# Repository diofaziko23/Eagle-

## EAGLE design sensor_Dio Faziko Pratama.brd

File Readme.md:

<!-- More info, tips and tricks for making GitHub Profile README can be found in my article at https://towardsdatascience.com/build-a-stunning-readme-for-your-github-profile-9b80434fe5d7 -->
<h1 align="center">Hi 👋, IM DIO FAZIKO PRATAMA</h1>
<h3 align="center">I am a student of the electronic engineering study program, Yogyakarta State University</h3>

- 🔭 I’m currently working on [Arduino and Artificial Intelligence](https://github.com/diofaziko23/arduino-project)
- 🔭 I’m currently working on [Arduino and Internet of Things](https://github.com/diofaziko23/arduino-project)
- 🌱 I’m currently learning **programming language,**
- 👨‍💻 All of my projects are available at [https://github.com/diofaziko23?tab=repositories](https://github.com/diofaziko23?tab=repositories)
- 📫 How to reach me **diofaziko.2021@student.uny.ac.id**.

<h3 align="left">Connect with me:</h3>
<p align="left">

</p>
<p align="left">

<h3 align="left">Languages and Tools:</h3>
<p align="left">              </p>

<p >&nbsp;</p>
<p align="left" >&nbsp;</p>

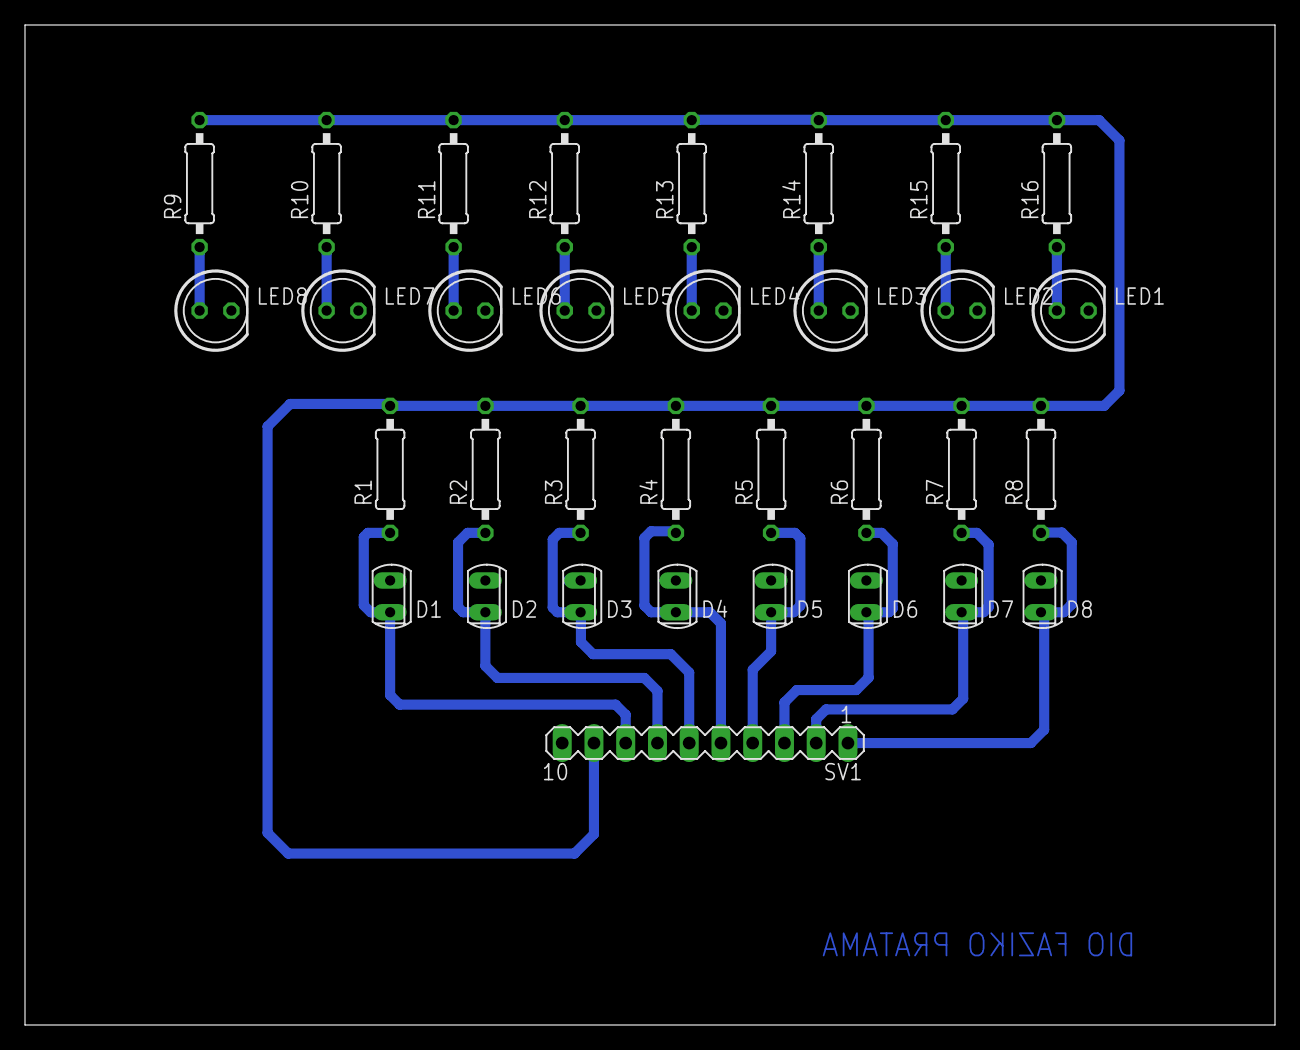
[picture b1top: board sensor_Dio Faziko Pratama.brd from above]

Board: 2 copper layers, 100.0 x 80.0 mm, 33 parts (0 on the bottom side), 18 nets.

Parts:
D1, D2, D3, D4, D5, D6, D7, D8: PhotoDioda; SFH225
LED1, LED2, LED3, LED4, LED5, LED6, LED7, LED8: LED putih SB; LED5MM
R1, R2, R3, R4, R5, R6, R7, R8: 0207/10
R9, R10, R11, R12, R13, R14, R15, R16: 330; 0207/10
SV1: MA10-1

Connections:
GND: D1.A, D2.A, D3.A, D4.A, D5.A, D6.A, D7.A, D8.A, LED1.K, LED2.K, LED3.K, LED4.K, LED5.K, LED6.K, LED7.K, LED8.K, SV1.10
unnamed: LED7.A, R10.1
unnamed: D7.K, R7.1, SV1.2
unnamed: D8.K, R8.1, SV1.1
unnamed: D1.K, R1.1, SV1.8
unnamed: D2.K, R2.1, SV1.7
unnamed: D3.K, R3.1, SV1.6
unnamed: D5.K, R5.1, SV1.4
unnamed: D4.K, R4.1, SV1.5
unnamed: D6.K, R6.1, SV1.3
unnamed: LED6.A, R11.1
unnamed: LED5.A, R12.1
unnamed: LED4.A, R13.1
unnamed: LED3.A, R14.1
unnamed: LED2.A, R15.1
unnamed: LED1.A, R16.1
unnamed: LED8.A, R9.1
VCC: R1.2, R2.2, R3.2, R4.2, R5.2, R6.2, R7.2, R8.2, R9.2, R10.2, R11.2, R12.2, R13.2, R14.2, R15.2, R16.2, SV1.9

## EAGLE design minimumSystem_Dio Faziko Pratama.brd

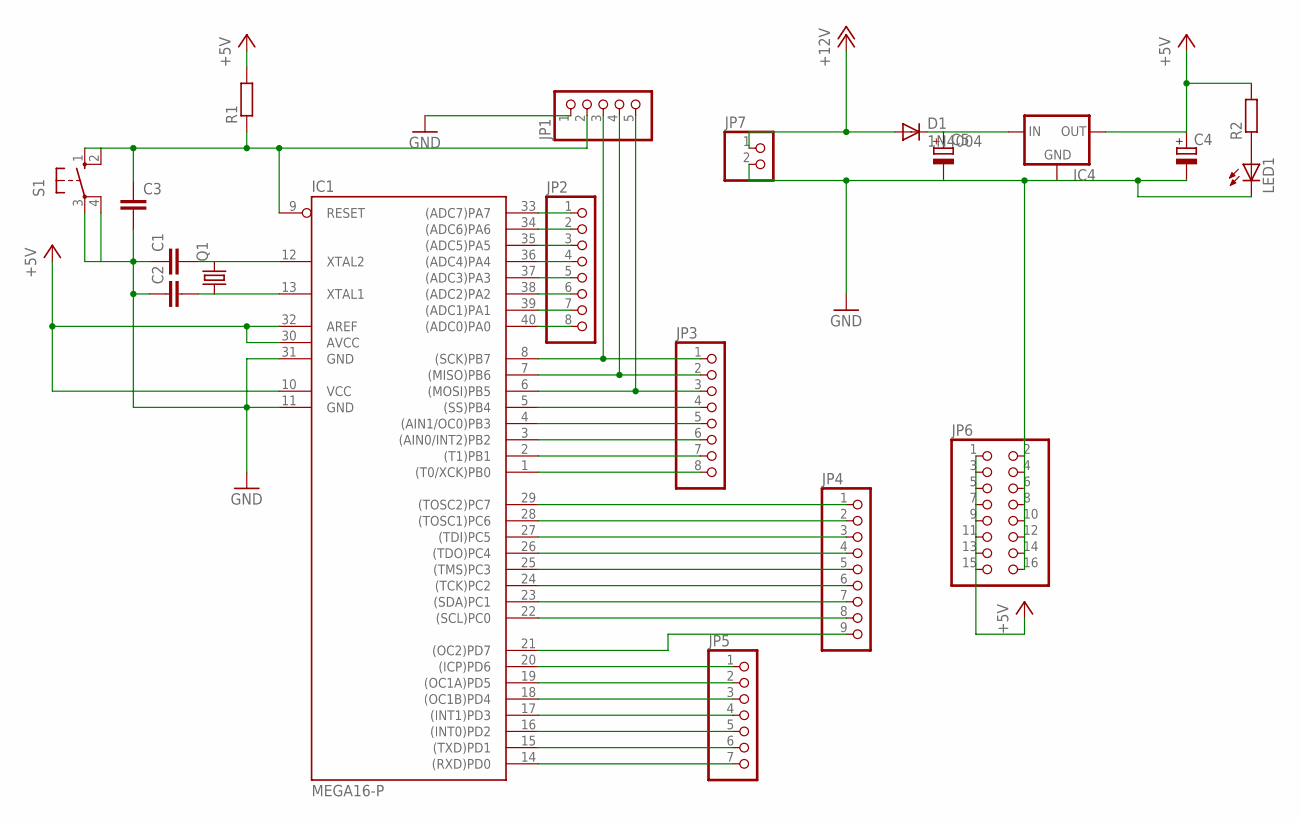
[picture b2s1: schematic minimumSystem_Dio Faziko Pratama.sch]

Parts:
C1, C2: C-EU025-024X044; C025-024X044
C3: C-EU050-025X075; C050-025X075
C4, C5: CPOL-EUE2.5-5; E2,5-5
D1: 1N4004; DO41-10
IC1: MEGA16-P; DIL40
IC4: 78XXS
JP1: PINHD-1X5; 1X05
JP2, JP3: PINHD-1X8; 1X08
JP4: PINHD-1X9; 1X09
JP5: PINHD-1X7; 1X07
JP6: PINHD-2X8; 2X08
JP7: PINHD-1X2; 1X02
LED1: LED5MM
Q1: CRYSTALHC49U-V; HC49U-V
R1, R2: R-EU_0204/7; 0204/7
S1: 10-XX; B3F-10XX

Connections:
+5V: C4.+, IC1.10 (VCC), IC1.30 (AVCC), IC1.32 (AREF), IC4.OUT, JP6.1, JP6.3, JP6.5, JP6.7, JP6.9, JP6.11, JP6.13, JP6.15, R1.2, R2.2
+12V: D1.A, JP7.1
C0: IC1.22 ((SCL)PC0), JP4.8
C1: IC1.23 ((SDA)PC1), JP4.7
C2: IC1.24 ((TCK)PC2), JP4.6
C3: IC1.25 ((TMS)PC3), JP4.5
D7: IC1.14 ((RXD)PD0), JP5.7
GND: C1.1, C2.1, C3.2, C4.-, C5.-, IC1.11 (GND), IC1.31 (GND), IC4.GND, JP1.1, JP6.2, JP6.4, JP6.6, JP6.8, JP6.10, JP6.12, JP6.14, JP6.16, JP7.2, LED1.K (C), S1.3, S1.4 (P1)
unnamed: IC1.33 ((ADC7)PA7), JP2.1
unnamed: IC1.34 ((ADC6)PA6), JP2.2
unnamed: IC1.35 ((ADC5)PA5), JP2.3
unnamed: IC1.36 ((ADC4)PA4), JP2.4
unnamed: IC1.37 ((ADC3)PA3), JP2.5
unnamed: IC1.38 ((ADC2)PA2), JP2.6
unnamed: IC1.39 ((ADC1)PA1), JP2.7
unnamed: IC1.40 ((ADC0)PA0), JP2.8
unnamed: IC1.29 ((TOSC2)PC7), JP4.1
unnamed: IC1.28 ((TOSC1)PC6), JP4.2
unnamed: IC1.27 ((TDI)PC5), JP4.3
unnamed: IC1.5 ((SS)PB4), JP3.4
unnamed: IC1.20 ((ICP)PD6), JP5.1
unnamed: IC1.19 ((OC1A)PD5), JP5.2
unnamed: IC1.26 ((TDO)PC4), JP4.4
unnamed: IC1.6 ((MOSI)PB5), JP1.5, JP3.3
unnamed: IC1.4 ((AIN1/OC0)PB3), JP3.5
unnamed: IC1.3 ((AIN0/INT2)PB2), JP3.6
unnamed: IC1.2 ((T1)PB1), JP3.7
unnamed: IC1.1 ((T0/XCK)PB0), JP3.8
unnamed: C5.+, D1.C, IC4.IN
unnamed: IC1.15 ((TXD)PD1), JP5.6
unnamed: IC1.16 ((INT0)PD2), JP5.5
unnamed: IC1.17 ((INT1)PD3), JP5.4
unnamed: C3.1, IC1.9 (RESET), JP1.2, R1.1, S1.1 (S), S1.2 (S1)
unnamed: IC1.18 ((OC1B)PD4), JP5.3
unnamed: C1.2, IC1.12 (XTAL2), Q1.2
unnamed: C2.2, IC1.13 (XTAL1), Q1.1
unnamed: LED1.A, R2.1
unnamed: IC1.8 ((SCK)PB7), JP1.3, JP3.1
unnamed: IC1.7 ((MISO)PB6), JP1.4, JP3.2
RS: IC1.21 ((OC2)PD7), JP4.9

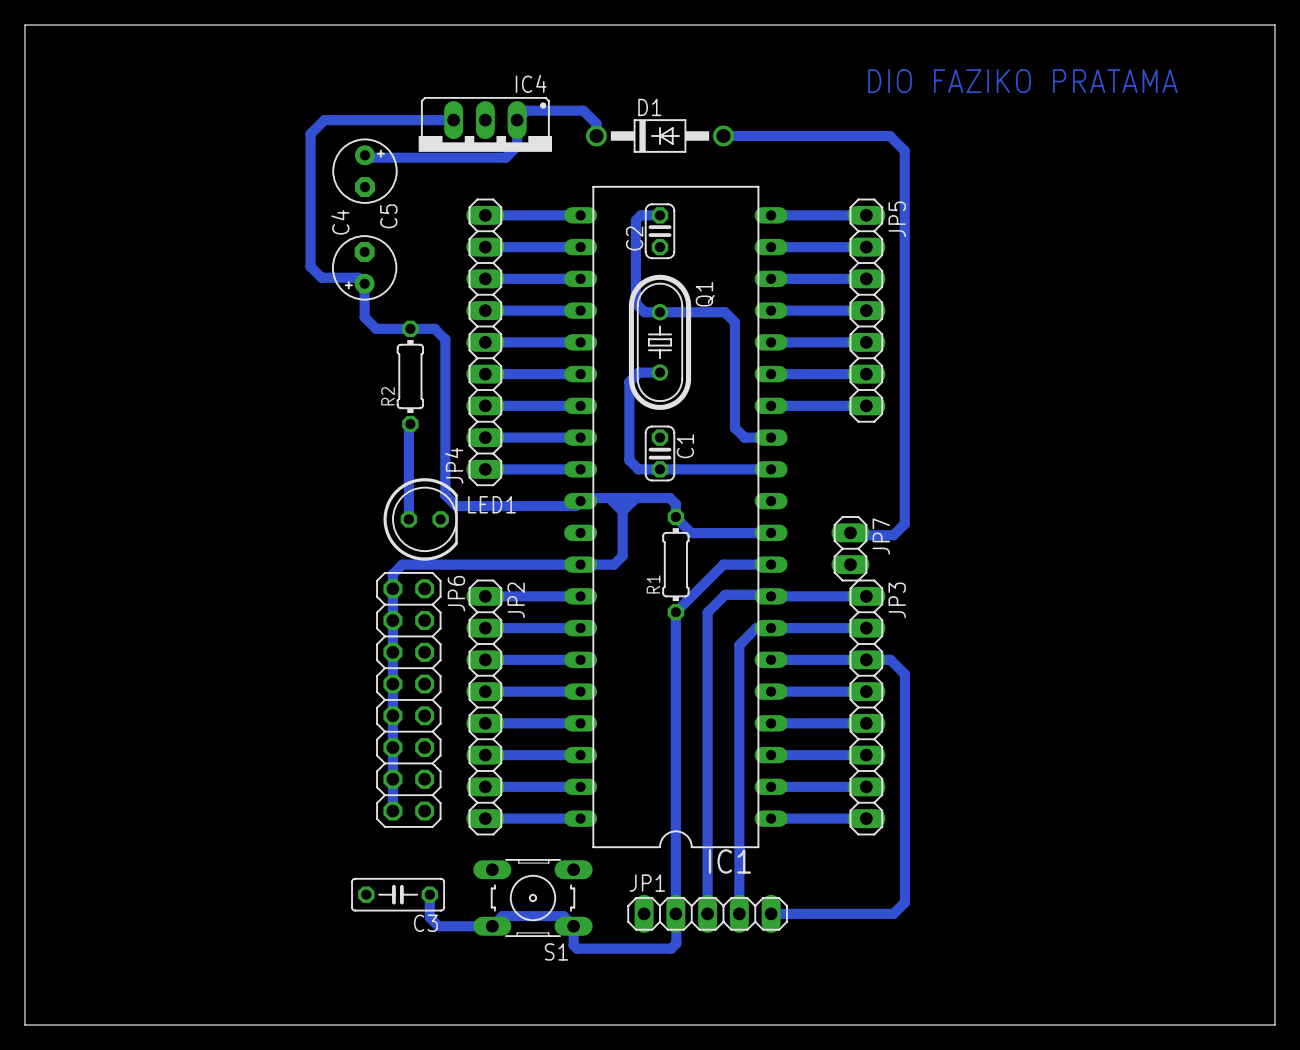
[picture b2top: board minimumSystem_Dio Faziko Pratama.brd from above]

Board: 2 copper layers, 100.0 x 80.0 mm, 20 parts (0 on the bottom side), 40 nets.

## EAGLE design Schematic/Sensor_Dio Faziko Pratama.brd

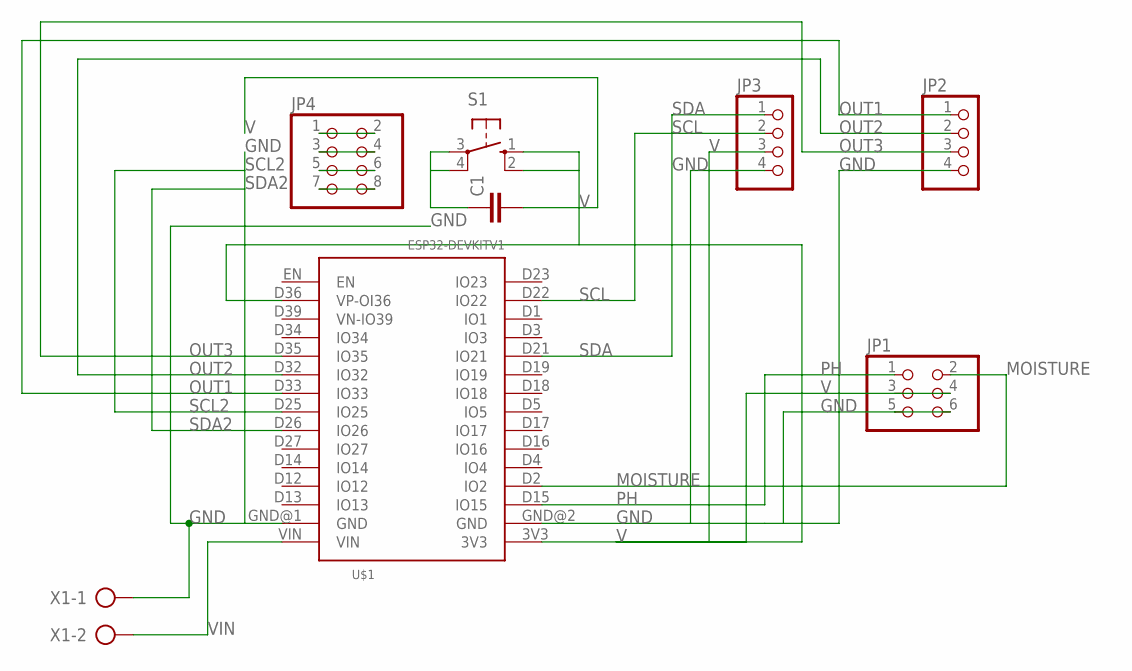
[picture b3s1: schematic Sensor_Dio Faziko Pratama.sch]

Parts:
C1: C-EU050-030X075; C050-030X075
JP1: PINHD-2X3; 2X03
JP2, JP3: PINHD-1X4; 1X04
JP4: PINHD-2X4; 2X04
S1: 10-XX; B3F-10XX
U$1: ESP32DEVKITV1; ESP32-DEVKITV1
X1: AK300/2

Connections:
GND: C1.1, JP1.5, JP1.6, JP2.4, JP3.4, JP4.3, JP4.4, S1.3, S1.4 (P1), U$1.GND@1 (GND), U$1.GND@2 (GND), X1.1
MOISTURE: JP1.2, U$1.D2 (IO2)
OUT1: JP2.1, U$1.D33 (IO33)
OUT2: JP2.2, U$1.D32 (IO32)
OUT3: JP2.3, U$1.D35 (IO35)
PH: JP1.1, U$1.D15 (IO15)
SCL: JP3.2, U$1.D22 (IO22)
SCL2: JP4.5, JP4.6, U$1.D25 (IO25)
SDA: JP3.1, U$1.D21 (IO21)
SDA2: JP4.7, JP4.8, U$1.D26 (IO26)
V: C1.2, JP1.3, JP1.4, JP3.3, JP4.1, JP4.2, S1.1 (S), S1.2 (S1), U$1.3V3, U$1.D36 (VP-OI36)
VIN: U$1.VIN, X1.2

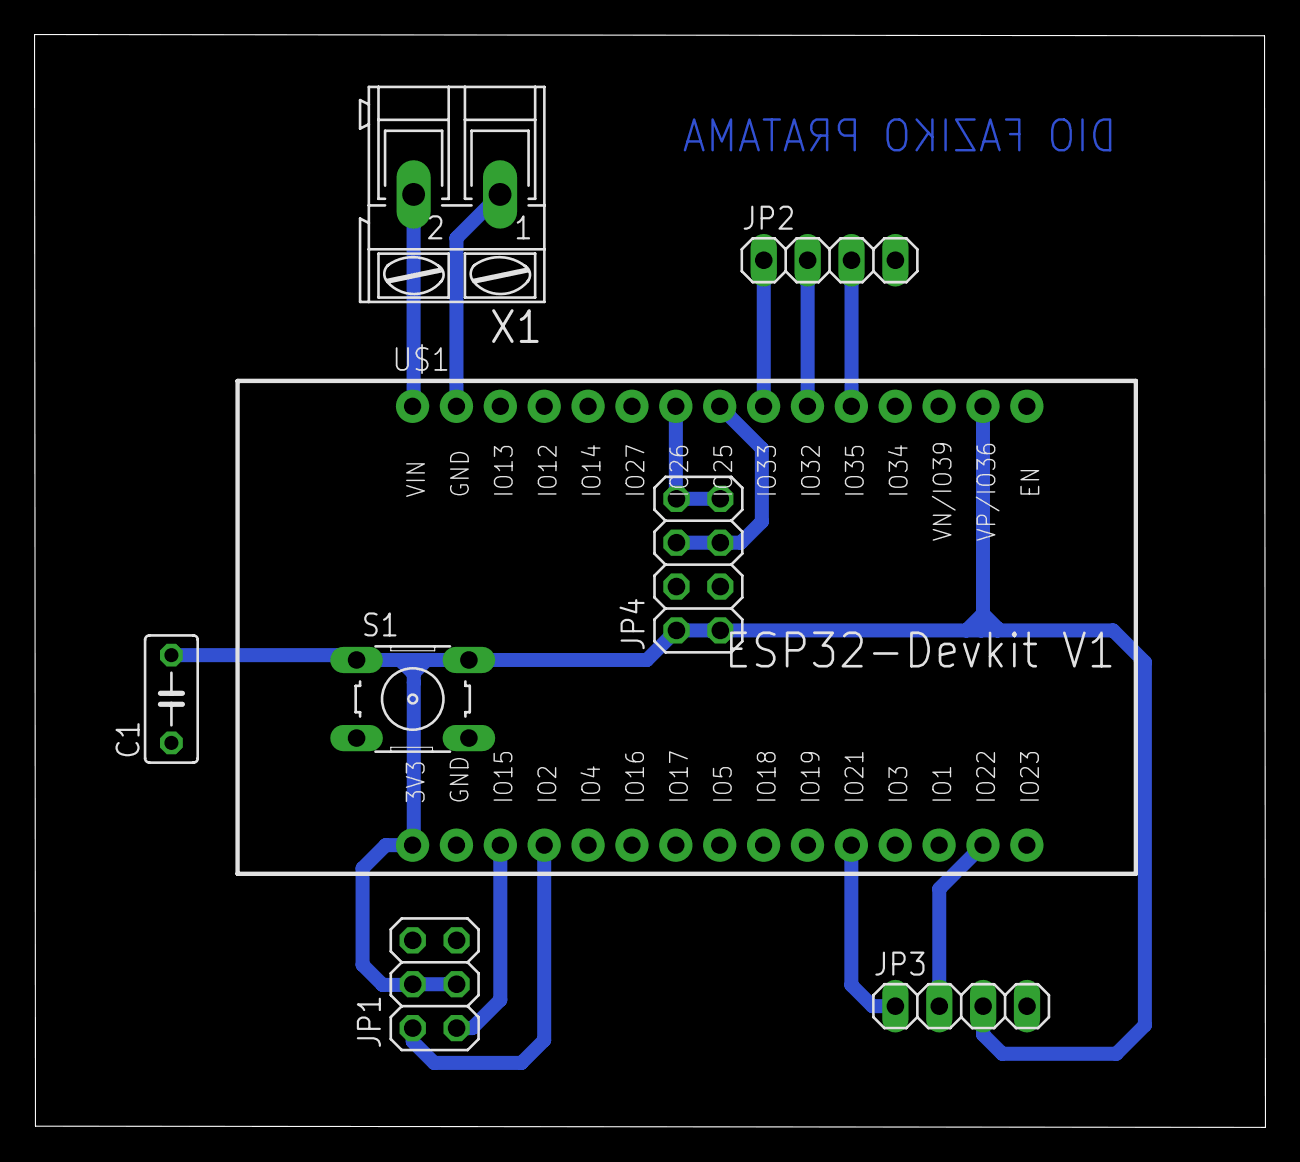
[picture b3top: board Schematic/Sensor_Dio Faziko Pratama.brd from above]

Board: 2 copper layers, 71.3 x 63.3 mm, 8 parts (0 on the bottom side), 12 nets.

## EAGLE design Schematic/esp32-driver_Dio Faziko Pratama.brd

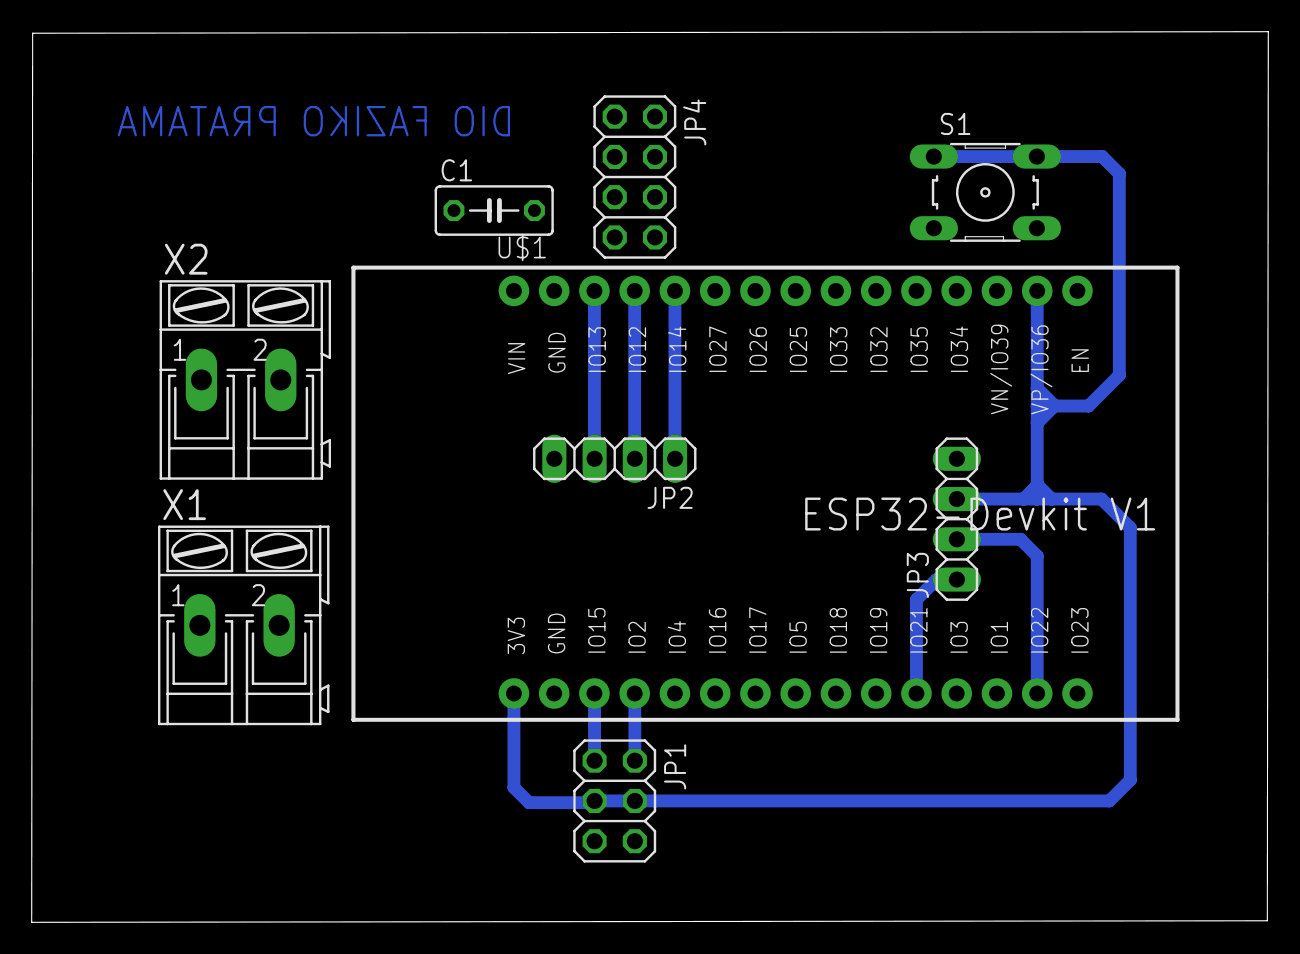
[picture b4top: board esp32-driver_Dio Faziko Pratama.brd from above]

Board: 2 copper layers, 78.0 x 56.2 mm, 9 parts (0 on the bottom side), 10 nets.

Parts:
C1: C050-030X075
JP1: 2X03
JP2, JP3: 1X04
JP4: 2X04
S1: B3F-10XX
U$1: ESP32DEVKITV1; ESP32-DEVKITV1
X1, X2: AK300/2

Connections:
GND: C1.1, JP1.5, JP1.6, JP2.4, JP3.4, JP4.3, JP4.4, S1.3, S1.4, U$1.GND@1, U$1.GND@2
MOISTURE: JP1.2, U$1.D2
OUT1: JP2.1, U$1.D14
OUT2: JP2.2, U$1.D12
OUT3: JP2.3, U$1.D13
PH: JP1.1, U$1.D15
S$1: JP4.1, JP4.2
SCL: JP3.2, U$1.D22
SDA: JP3.1, U$1.D21
V: JP1.3, JP1.4, JP3.3, S1.1, S1.2, U$1.3V3, U$1.D36

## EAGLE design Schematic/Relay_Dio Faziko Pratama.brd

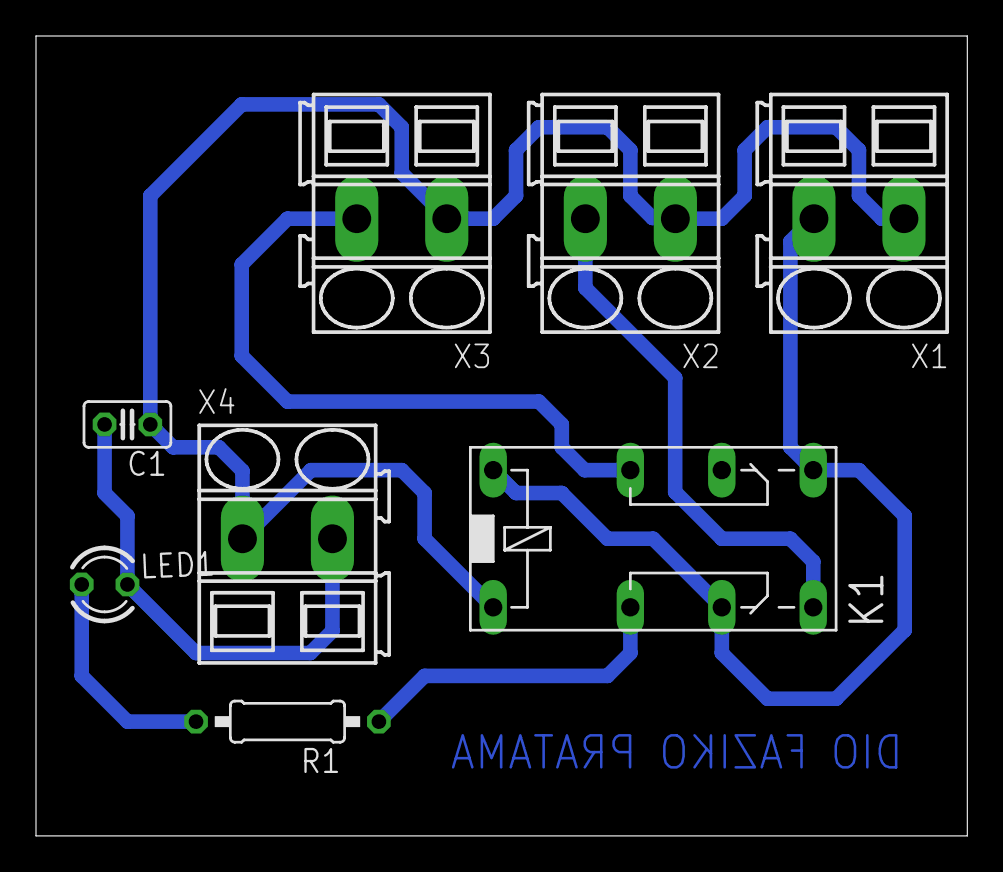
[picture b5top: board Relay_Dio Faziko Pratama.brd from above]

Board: 2 copper layers, 51.7 x 44.4 mm, 8 parts (0 on the bottom side), 7 nets.

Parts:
C1: C025-025X050
K1: 351
LED1: LED3MM
R1: 0207/10
X1, X2, X3, X4: SMKDSP_1,5/2

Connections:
GND: C1.1, K1.1, X1.1, X2.1, X3.1, X4.1
unnamed: K1.P1, R1.1
unnamed: LED1.A, R1.2
O1: K1.S1, X2.2
P2: K1.P2, X3.2
S12: K1.16, K1.O1, K1.S2, X1.2
VOUT: C1.2, LED1.K, X4.2

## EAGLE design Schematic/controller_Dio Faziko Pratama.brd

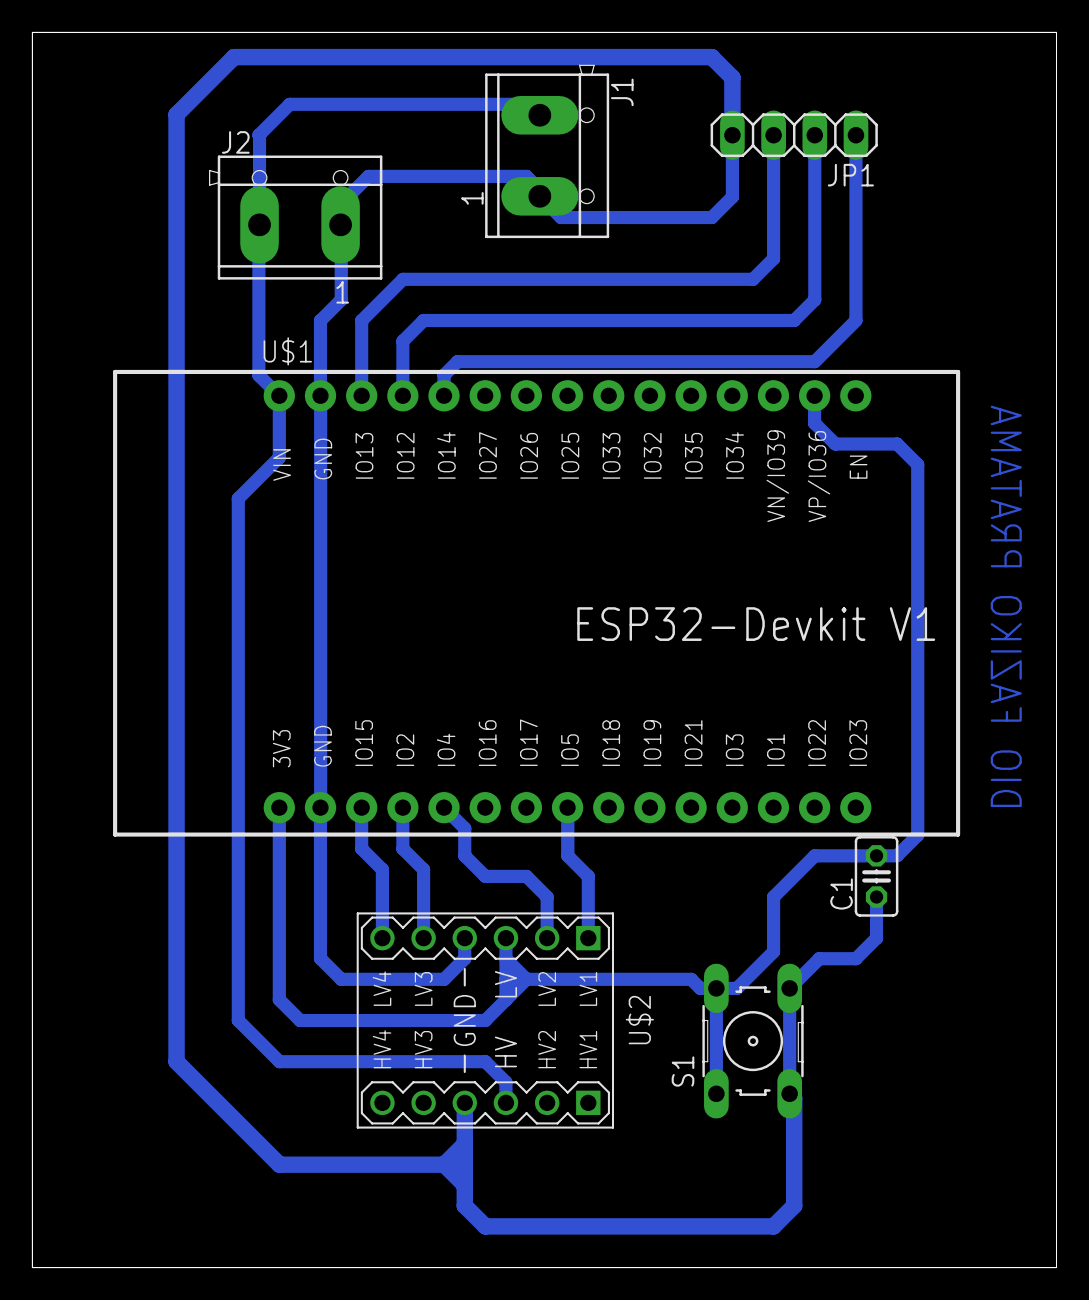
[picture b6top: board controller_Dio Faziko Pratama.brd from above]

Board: 2 copper layers, 63.2 x 76.2 mm, 7 parts (0 on the bottom side), 10 nets.

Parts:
C1: C025-025X050
J1, J2: CON_TERMINAL_BLOCK_02-5MM; TERMINAL_BLOCK_2P_5
JP1: 1X04
S1: B3F-10XX
U$1: ESP32DEVKITV1; ESP32-DEVKITV1
U$2: LEVEL-SHIFTER-4CH

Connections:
GND: C1.1, J1.1, J2.1, JP1.4, S1.3, S1.4, U$1.GND@1, U$1.GND@2, U$2.J1.4, U$2.J2.4
HV: J1.2, J2.2, U$1.VIN, U$2.J2.3
LV: C1.2, S1.1, S1.2, U$1.3V3, U$1.D36, U$2.J1.3
LV1: U$1.D5, U$2.J1.1
LV2: U$1.D4, U$2.J1.2
LV3: U$1.D2, U$2.J1.5
LV4: U$1.D15, U$2.J1.6
OUT1: JP1.1, U$1.D14
OUT2: JP1.2, U$1.D12
OUT3: JP1.3, U$1.D13

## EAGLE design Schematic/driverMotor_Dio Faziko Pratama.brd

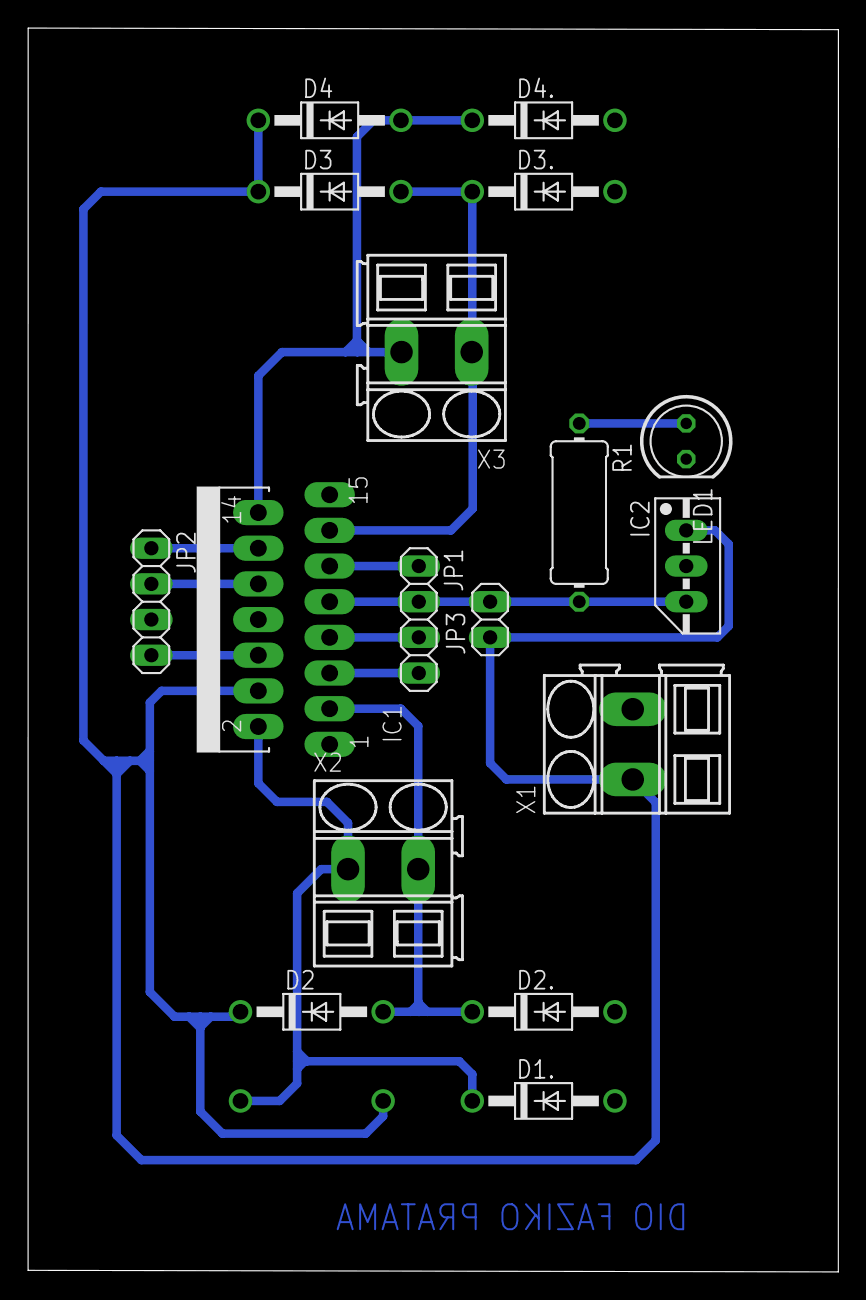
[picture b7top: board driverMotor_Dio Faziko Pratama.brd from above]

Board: 2 copper layers, 57.7 x 88.6 mm, 18 parts (1 on the bottom side), 14 nets.

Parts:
D1, D1., D2, D2., D3, D3., D4, D4.: 1N4004; DO41-10
IC1: L298; MULTIWATT-15
IC2: 78MXXS
JP1, JP2: 1X04
JP3: 1X02
LED1: LED5MM
R1: 0411/12
X1, X2, X3: SMKDSP_1,5/2

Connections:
+5V: IC1.9, IC2.OUT, JP1.2, JP3.2, R1.2
ENABLE_A: IC1.6, JP2.4
ENABLE_B: IC1.11, JP1.1
GND: D1..A, D2..A, D3..A, D4..A, IC1.1, IC1.8, IC1.15, IC2.GND, JP2.3, LED1.K, X1.2
INPUT1: IC1.5, JP1.4
INPUT2: IC1.7, JP1.3
INPUT3: IC1.10, JP2.2
INPUT4: IC1.12, JP2.1
LED: LED1.A, R1.1
MOTOR1_1: D1.A, D1..C, IC1.2, X2.1
MOTOR1_2: D2.A, D2..C, IC1.3, X2.2
MOTOR2_1: D3.A, D3..C, IC1.13, X3.1
MOTOR2_2: D4.A, D4..C, IC1.14, X3.2
VS: D1.C, D2.C, D3.C, D4.C, IC1.4, IC2.IN, JP3.1, X1.1

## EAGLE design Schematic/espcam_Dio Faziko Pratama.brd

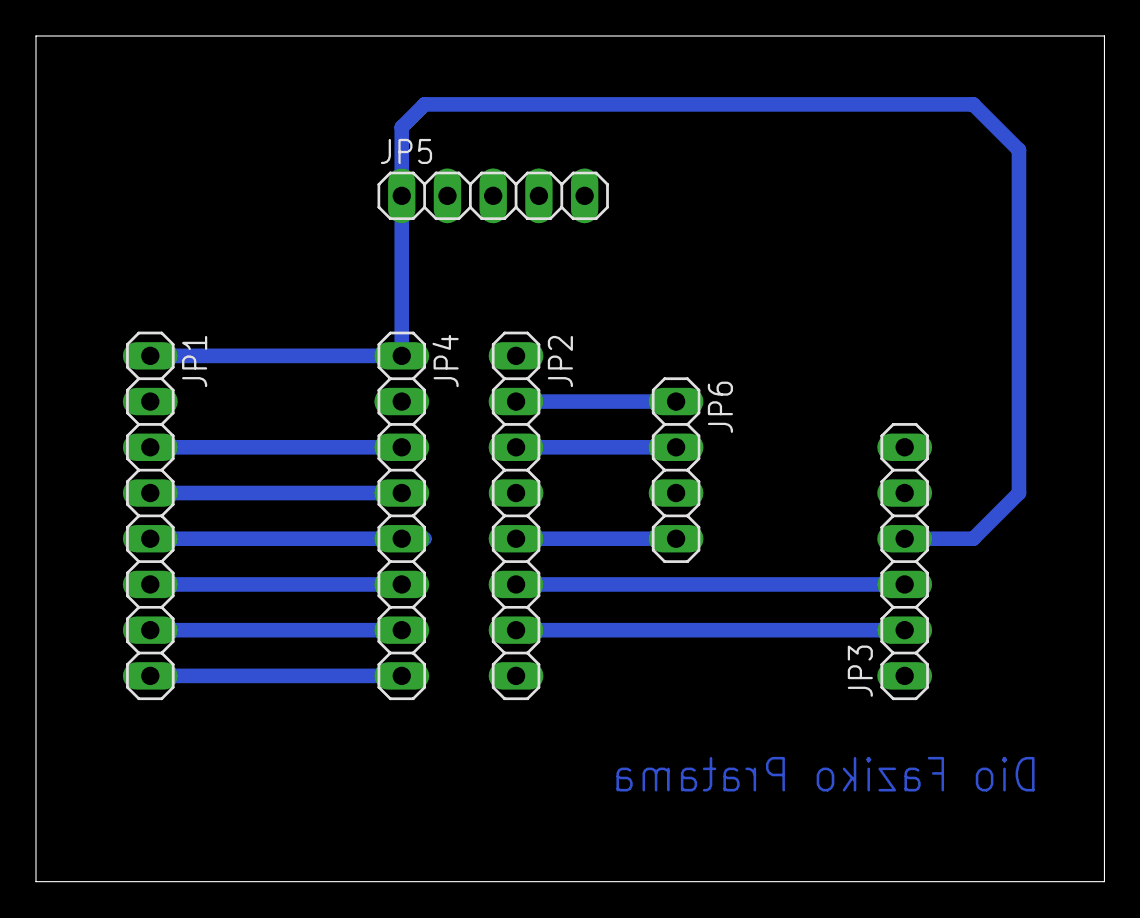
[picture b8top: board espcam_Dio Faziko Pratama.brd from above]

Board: 2 copper layers, 59.4 x 47.0 mm, 6 parts (0 on the bottom side), 13 nets.

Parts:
JP1, JP2, JP4: 1X08
JP3: 1X06
JP5: 1X05
JP6: 1X04

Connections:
5V: JP1.1, JP3.4, JP4.1, JP5.1
GND: JP1.2, JP2.4, JP2.8, JP3.6, JP4.2, JP6.3
IO0: JP2.3, JP6.2
IO2: JP1.7, JP4.7
IO4: JP1.8, JP4.8
IO12: JP1.3, JP4.3
IO13: JP1.4, JP4.4
IO14: JP1.6, JP4.6
IO15: JP1.5, JP4.5
IO16: JP2.2, JP6.1
RX: JP2.7, JP3.2
TX: JP2.6, JP3.3
VOUT: JP2.5, JP6.4

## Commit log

2021-12-26 Rename Profil.md to Readme.md

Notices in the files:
parts and their libraries:
diy-model: Released under the Creative Commons Attribution 4.0 International License: http://creativecommons.org/licenses/by/4.0
